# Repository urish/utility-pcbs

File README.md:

# utility-PCBS

* [APA102-2020 Stick](apa102-2020-stick.brd)
* [WSON6 and SOT23-5 breakout](breakout-wson6-sot23-5.brd)

Copyright (C) 2017, Uri Shaked

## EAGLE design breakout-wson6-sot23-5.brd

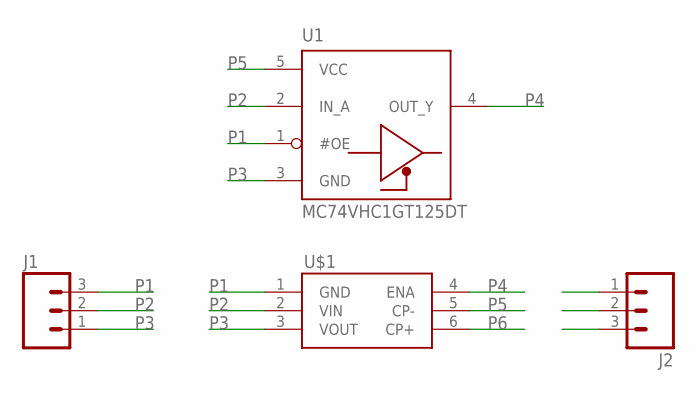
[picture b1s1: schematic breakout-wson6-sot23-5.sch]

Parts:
J1, J2: M03LOCK; 1X03_LOCK
U1: MC74VHC1GT125DT; SOT23-5
U$1: TPS60150; WSON6

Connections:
P1: J1.3, U1.1 (#OE), U$1.1 (GND)
P2: J1.2, U1.2 (IN_A), U$1.2 (VIN)
P3: J1.1, U1.3 (GND), U$1.3 (VOUT)
P4: J2.3, U1.4 (OUT_Y), U$1.4 (ENA)
P5: J2.2, U1.5 (VCC), U$1.5 (CP-)
P6: J2.1, U$1.6 (CP+)

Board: 2 copper layers, 4 parts (1 on the bottom side), 6 nets, no tracks yet.

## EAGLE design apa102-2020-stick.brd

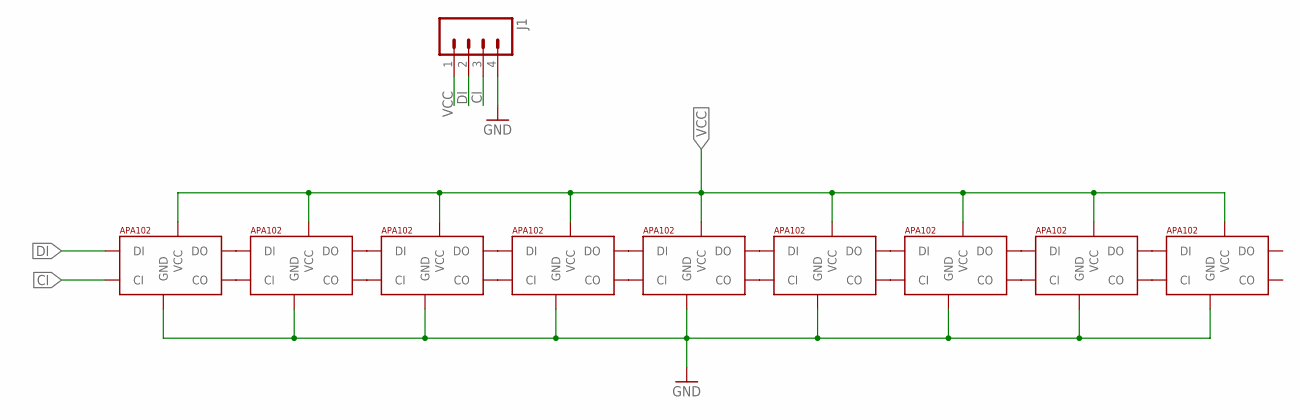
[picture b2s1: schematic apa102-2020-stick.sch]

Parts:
J1: M04LOCK; 1X04_LOCK
U$1, U$2, U$3, U$4, U$5, U$6, U$7, U$8, U$9: APA1022020; APA102_2020

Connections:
CI: J1.3, U$1.C_IN (CI)
DI: J1.2, U$1.D_IN (DI)
GND: J1.4, U$1.GND, U$2.GND, U$3.GND, U$4.GND, U$5.GND, U$6.GND, U$7.GND, U$8.GND, U$9.GND
unnamed: U$1.D_OUT (DO), U$2.D_IN (DI)
unnamed: U$1.CL_OUT (CO), U$2.C_IN (CI)
unnamed: U$2.D_OUT (DO), U$3.D_IN (DI)
unnamed: U$2.CL_OUT (CO), U$3.C_IN (CI)
unnamed: U$3.D_OUT (DO), U$4.D_IN (DI)
unnamed: U$3.CL_OUT (CO), U$4.C_IN (CI)
unnamed: U$4.D_OUT (DO), U$5.D_IN (DI)
unnamed: U$4.CL_OUT (CO), U$5.C_IN (CI)
unnamed: U$5.D_OUT (DO), U$6.D_IN (DI)
unnamed: U$5.CL_OUT (CO), U$6.C_IN (CI)
unnamed: U$6.D_OUT (DO), U$7.D_IN (DI)
unnamed: U$6.CL_OUT (CO), U$7.C_IN (CI)
unnamed: U$7.D_OUT (DO), U$8.D_IN (DI)
unnamed: U$7.CL_OUT (CO), U$8.C_IN (CI)
unnamed: U$8.D_OUT (DO), U$9.D_IN (DI)
unnamed: U$8.CL_OUT (CO), U$9.C_IN (CI)
VCC: J1.1, U$1.V_CC (VCC), U$2.V_CC (VCC), U$3.V_CC (VCC), U$4.V_CC (VCC), U$5.V_CC (VCC), U$6.V_CC (VCC), U$7.V_CC (VCC), U$8.V_CC (VCC), U$9.V_CC (VCC)

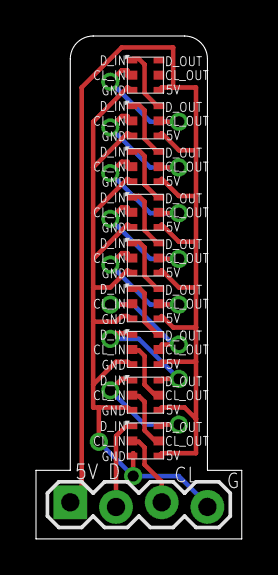
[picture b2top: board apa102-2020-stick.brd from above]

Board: 2 copper layers, 11.4 x 27.9 mm, 10 parts (0 on the bottom side), 20 nets.

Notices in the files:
parts and their libraries:
SparkFun-Connectors: Licensing: Creative Commons ShareAlike 4.0 International - https://creativecommons.org/licenses/by-sa/4.0
